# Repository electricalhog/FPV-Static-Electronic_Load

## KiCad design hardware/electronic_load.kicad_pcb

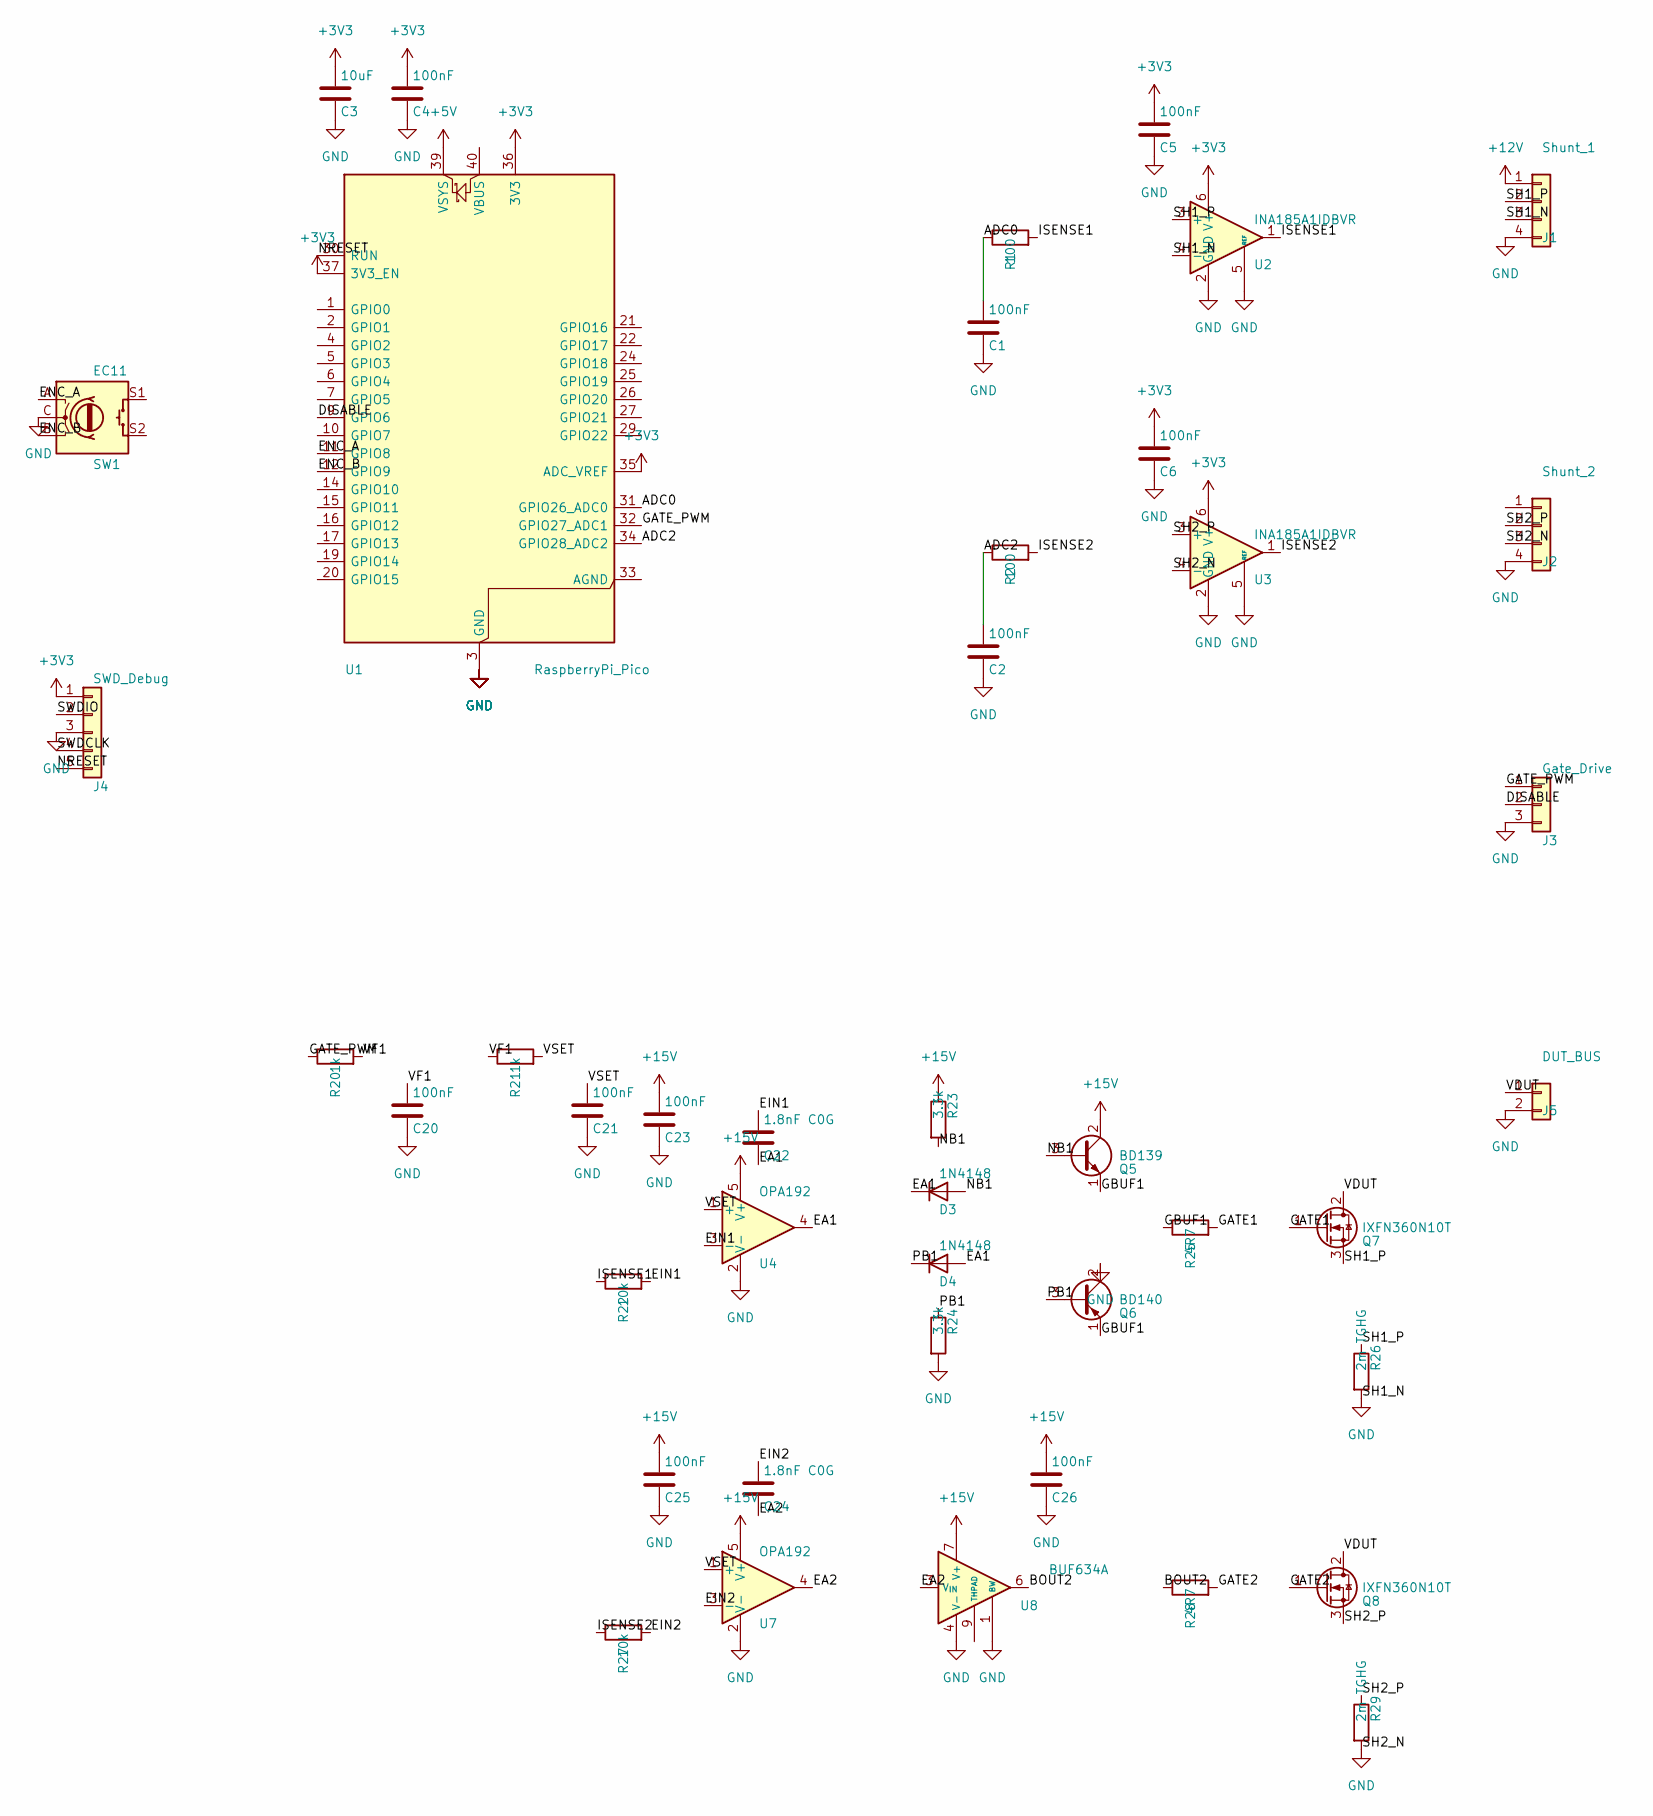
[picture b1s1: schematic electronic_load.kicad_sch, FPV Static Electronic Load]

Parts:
C1, C2, C4, C5, C6, C20, C21, C23, C25, C26: 100nF; C_0603_1608Metric
C3: 10uF; C_0805_2012Metric
C22, C24: 1.8nF C0G; C_0603_1608Metric
D3, D4: 1N4148; D_DO-35_SOD27_P7.62mm_Horizontal
J1: Shunt_1; PinHeader_1x04_P2.54mm_Vertical
J2: Shunt_2; PinHeader_1x04_P2.54mm_Vertical
J3: Gate_Drive; PinHeader_1x03_P2.54mm_Vertical
J4: SWD_Debug; PinHeader_1x05_P2.54mm_Vertical
J5: DUT_BUS; PinHeader_1x02_P2.54mm_Vertical
Q5: BD139; TO-126-3_Vertical
Q6: BD140; TO-126-3_Vertical
Q7, Q8: IXFN360N10T; SOT-227
R1, R2: 100; R_0603_1608Metric
R20, R21: 1k; R_0603_1608Metric
R22, R27: 10k; R_0603_1608Metric
R23, R24: 3.3k; R_0603_1608Metric
R25, R28: 4R7; R_0603_1608Metric
R26, R29: 2m TGHG; SOT-227
SW1: EC11; RotaryEncoder_Alps_EC11E-Switch_Vertical_H20mm
U1: RaspberryPi_Pico
U2, U3: INA185A1IDBVR; SOT-23-5
U4, U7: OPA192; SOT-23-5
U8: BUF634A; HSOP-8-1EP_3.9x4.9mm_P1.27mm_EP2.41x3.1mm

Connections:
+3V3: C3.1, C4.1, C5.1, C6.1, J4.1, U1.35 (ADC_VREF), U1.36 (3V3), U1.37 (3V3_EN), U2.6 (V+), U3.6 (V+)
+5V: U1.39 (VSYS)
+12V: J1.1
+15V: C23.1, C25.1, C26.1, Q5.2 (C), R23.1, U4.5 (V+), U7.5 (V+), U8.7 (V+)
/ADC0: C1.1, R1.1, U1.31 (GPIO26_ADC0)
/ADC2: C2.1, R2.1, U1.34 (GPIO28_ADC2)
/BOUT2: R28.1, U8.6
/DISABLE: J3.2, U1.9 (GPIO6)
/EA1: C22.2, D3.1 (K), D4.2 (A), U4.4
/EA2: C24.2, U7.4, U8.3 (V_{IN})
/EIN1: C22.1, R22.2, U4.3 (-)
/EIN2: C24.1, R27.2, U7.3 (-)
/ENC_A: SW1.A, U1.11 (GPIO8)
/ENC_B: SW1.B, U1.12 (GPIO9)
/GATE1: Q7.1 (G), R25.2
/GATE2: Q8.1 (G), R28.2
/GATE_PWM: J3.1, R20.1, U1.32 (GPIO27_ADC1)
/GBUF1: Q5.1 (E), Q6.1 (E), R25.1
/ISENSE1: R1.2, R22.1, U2.1
/ISENSE2: R2.2, R27.1, U3.1
/NB1: D3.2 (A), Q5.3 (B), R23.2
/NRESET: J4.5, U1.30 (RUN)
/PB1: D4.1 (K), Q6.3 (B), R24.1
/SH1_P: J1.2, Q7.3 (S), R26.1, U2.3 (+)
/SH2_P: J2.2, Q8.3 (S), R29.1, U3.3 (+)
/SWDCLK: J4.4
/SWDIO: J4.2
/VDUT: J5.1, Q7.2 (D), Q8.2 (D)
/VF1: C20.1, R20.2, R21.1
/VSET: C21.1, R21.2, U4.1 (+), U7.1 (+)
GND: C1.2, C2.2, C3.2, C4.2, C5.2, C6.2, C20.2, C21.2, C23.2, C25.2, C26.2, J1.3, J1.4, J2.3, J2.4, J3.3, J4.3, J5.2, Q6.2 (C), R24.2, R26.2, R29.2, SW1.C, U1.3 (GND), U1.8 (GND), U1.13 (GND), U1.18 (GND), U1.23 (GND), U1.28 (GND), U1.38 (GND), U2.2 (GND), U2.4 (-), U2.5 (REF), U3.2 (GND), U3.4 (-), U3.5 (REF), U4.2 (V-), U7.2 (V-), U8.1 (BW), U8.4 (V-)

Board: 2 copper layers, 43 parts (0 on the bottom side), 27 nets, no tracks yet.

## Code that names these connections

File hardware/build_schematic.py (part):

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u1_adc_vref   = pin('U1', '35')          # ADC_VREF
u1_gnd        = pin('U1', '3')           # first GND
u1_agnd       = pin('U1', '33')          # AGND (analog GND)
u1_gpio6      = pin('U1', '9')           # DISABLE
u1_gpio8      = pin('U1', '11')          # ENC_A
u1_gpio9      = pin('U1', '12')          # ENC_B
u1_adc0       = pin('U1', '31')          # GPIO26_ADC0
u1_pwm        = pin('U1', '32')          # GPIO27_ADC1 → gate PWM
u1_adc2       = pin('U1', '34')          # GPIO28_ADC2
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j4 = {str(n): pin('J4', str(n)) for n in range(1, 6)}

# Additional U1 pins
u1_run    = pin('U1', '30')   # RUN / nRESET
u1_3v3_en = pin('U1', '37')   # 3V3_EN – must be pulled high to enable regulator
u1_gnd38  = pin('U1', '38')   # GND (bottom)
u1_vsys   = pin('U1', '39')   # VSYS power input (5 V supply)
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nets = [
    # Encoder quadrature to Pico
    ('ENC_A',    *sw1_a),
    ('ENC_A',    *u1_gpio8),
    ('ENC_B',    *sw1_b),
    ('ENC_B',    *u1_gpio9),

    # INA1 output → series R1 → ADC0
    ('ISENSE1',  *u2_out),
    ('ISENSE1',  *r1_ina),   # right pin of R1 (INA side)
    ('ADC0',     *r1_adc),   # left  pin of R1 (filter output)
    ('ADC0',     *u1_adc0),

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    # Gate drive (PWM5B) and load enable
    ('GATE_PWM', *u1_pwm),
    ('GATE_PWM', *j3['1']),
    ('DISABLE',  *u1_gpio6),
    ('DISABLE',  *j3['2']),

    # Shunt sense inputs to INA1
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    # SWD debug connector J4 signals
    ('SWDIO',    *j4['2']),   # J4 pin 2 – data (no matching Pico module pin)
    ('SWDCLK',   *j4['4']),   # J4 pin 4 – clock (no matching Pico module pin)
    ('NRESET',   *j4['5']),   # J4 pin 5 – reset
    ('NRESET',   *u1_run),    # U1 pin 30 (RUN) = active-high reset
]

for net, x, y in nets:
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    ('EA1',      *d3_k), ('EA1', *d4_a),          # class-AB input node
    # bias chain and output pair
    ('NB1',      *r23_b), ('NB1', *d3_a), ('NB1', *q5['3']),
    ('PB1',      *r24_t), ('PB1', *d4_k), ('PB1', *q6['3']),
    ('GBUF1',    *q5['1']), ('GBUF1', *q6['1']), ('GBUF1', *r25_l),
    ('GATE1',    *r25_r), ('GATE1', *q7['1']),
    # power FET + TGHG shunt (SOT-227 pair on shared heatsink)
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
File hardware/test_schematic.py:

"""
Schematic completeness tests for FPV Static Electronic Load.
Run:  pytest hardware/test_schematic.py -v
"""
import os, sys, glob
import pytest

SITE = '/home/daniel/.cache/uv/archive-v0/7cuypMzPSfPk6TCt/lib/python3.12/site-packages'
SCH  = '/home/daniel/GitHub/FPV-Static-Electronic_Load/hardware/electronic_load.kicad_sch'


def _find_symlib():
    """Same resolution as build_schematic.py: env var, flatpak (any hash), apt."""
    if p := os.environ.get('KICAD_SYMBOL_DIR'):
        return p
    probe = 'MCU_Module.kicad_sym'
    for m in reversed(sorted(glob.glob(
            '/var/lib/flatpak/runtime/org.kicad.KiCad.Library.Symbols'
            '/x86_64/stable/*/files/symbols'))):
        if os.path.exists(os.path.join(m, probe)):
            return m
    return '/usr/share/kicad/symbols'


SYMLIB = _find_symlib()
sys.path.insert(0, SITE)
os.environ['KICAD_SYMBOL_DIR']  = SYMLIB
os.environ['KICAD6_SYMBOL_DIR'] = SYMLIB

from kicad_sch_api import load_schematic


@pytest.fixture(scope='module')
def sch():
    return load_schematic(SCH)


# ── Net labels ──────────────────────────────────────────────────────────────

SIGNAL_NETS = [
    'ENC_A', 'ENC_B',
    'ISENSE1', 'ADC0',
    'ISENSE2', 'ADC2',
    'GATE_PWM', 'DISABLE',
    'SH1_P', 'SH1_N',
    'SH2_P', 'SH2_N',
]

SWD_NETS = ['SWDIO', 'SWDCLK', 'NRESET']

# Analog frontend (per-FET linear loops; see hardware/sim/)
ANALOG_NETS = [
    'VF1', 'VSET',                          # setpoint DAC filter
    'EIN1', 'EA1', 'NB1', 'PB1', 'GBUF1', 'GATE1',   # ch A discrete class-AB
    'EIN2', 'EA2', 'BOUT2', 'GATE2',                 # ch B BUF634A
    'VDUT',                                          # shared drain bus
]


def _label_counts(sch):
    from collections import Counter
    return Counter(l.text for l in sch.labels)


def test_signal_nets_each_appear_twice(sch):
    counts = _label_counts(sch)
    missing = [n for n in SIGNAL_NETS if counts[n] < 2]
    assert not missing, f"Nets with fewer than 2 label endpoints: {missing}"


def test_swd_nets_present(sch):
    counts = _label_counts(sch)
    missing = [n for n in SWD_NETS if counts[n] < 1]
    assert not missing, f"SWD net labels missing: {missing}"


def test_analog_nets_each_appear_twice(sch):
    counts = _label_counts(sch)
    missing = [n for n in ANALOG_NETS if counts[n] < 2]
    assert not missing, f"Analog nets with fewer than 2 label endpoints: {missing}"


def test_vdut_bus_reaches_both_fets_and_connector(sch):
    counts = _label_counts(sch)
    assert counts['VDUT'] >= 3, (
        f"VDUT should appear on Q7 drain, Q8 drain and J5: got {counts['VDUT']}"
    )


def test_both_gate_buffer_variants_present(sch):
    refs = {c.reference: c.value for c in sch.components.all()}
    # discrete class-AB variant
    assert refs.get('Q5') == 'BD139' and refs.get('Q6') == 'BD140'
    # all-in-one variant
    assert refs.get('U8', '').startswith('BUF634')
    # both power FETs and TGHG shunts
    assert refs.get('Q7') == 'IXFN360N10T' and refs.get('Q8') == 'IXFN360N10T'
    assert refs.get('R26') == '2m TGHG' and refs.get('R29') == '2m TGHG'


# ── Power symbols ───────────────────────────────────────────────────────────

def test_power_symbols_use_pwr_reference(sch):
    bad = [
        comp.reference
        for comp in sch.components.all()
        if comp.lib_id.startswith('power:')
        and not comp.reference.startswith('#PWR')
    ]
    assert not bad, f"Power symbols with wrong reference prefix: {bad}"


# ── U1 Pico power/control pins ──────────────────────────────────────────────

def _power_lib_ids_at(sch, x, y, tol=0.5):
    return [
        c.lib_id for c in sch.components.all()
        if c.lib_id.startswith('power:')
        and abs(c.position.x - x) < tol
        and abs(c.position.y - y) < tol
    ]


def test_u1_vsys_has_power_symbol(sch):
    # U1 pin 39 (VSYS) must have a power symbol placed at its position
    pos = sch.get_component_pin_position('U1', '39')
    found = _power_lib_ids_at(sch, pos.x, pos.y)
    assert found, f"No power symbol at U1 VSYS pin ({pos.x}, {pos.y})"


def test_u1_run_has_nreset_label(sch):
    # U1 pin 30 (RUN) should be driven by NRESET label or tied to 3V3
    pos = sch.get_component_pin_position('U1', '30')
    labels_here = [
        l.text for l in sch.labels
        if abs(l.position.x - pos.x) < 0.5 and abs(l.position.y - pos.y) < 0.5
    ]
    pwr_here = _power_lib_ids_at(sch, pos.x, pos.y)
    assert labels_here or pwr_here, (
        f"U1 RUN pin ({pos.x}, {pos.y}) has neither a label nor a power symbol"
    )


def test_u1_remaining_gnd_pins_connected(sch):
    # Passive GND pins: 8, 13, 18, 23, 28, 38
    gnd_pins = ['8', '13', '18', '23', '28', '38']
    missing = []
    for pnum in gnd_pins:
        pos = sch.get_component_pin_position('U1', pnum)
        found = _power_lib_ids_at(sch, pos.x, pos.y)
        if not found:
            missing.append(pnum)
    assert not missing, f"U1 GND pins without power symbols: {missing}"


# ── RC filter wires ─────────────────────────────────────────────────────────

def test_rc_filter_wires_exist(sch):
    wires = list(sch.wires)
    assert len(wires) >= 2, "Expected ≥2 RC filter wires (R→C stubs)"


def test_rc_filter_wires_are_vertical(sch):
    for w in sch.wires:
        pts = w.points
        assert abs(pts[0].x - pts[1].x) < 0.01, (
            f"RC filter wire should be vertical, got x={pts[0].x} vs {pts[1].x}"
        )

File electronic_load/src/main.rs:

#![no_std]
#![no_main]

use panic_halt as _;
use rp2040_hal as hal;
use hal::pac;
use embedded_hal::{digital::OutputPin, pwm::SetDutyCycle};
use embedded_hal_0_2::adc::OneShot;
use rotary_encoder_embedded::{Direction, RotaryEncoder};

#[link_section = ".boot2"]
#[used]
pub static BOOT2: [u8; 256] = rp2040_boot2::BOOT_LOADER_GENERIC_03H;

// ── Tuning constants ──────────────────────────────────────────────────────────

/// Control loop sample period. 500 µs = 2 kHz.
const SAMPLE_PERIOD_US: u64 = 500;

/// Current setpoint change per encoder click, milliamps.
const ENCODER_STEP_MA: u32 = 100;

/// Hard ceiling on the setpoint, milliamps.
const MAX_SETPOINT_MA: u32 = 20_000;

/// Soft-start ramp: milliamps added to the active setpoint per control tick.
/// At 2 kHz: 10 mA × 2000 ticks/s = 20 A/s ramp rate.
const SOFT_START_RAMP_MA_PER_TICK: u32 = 10;

/// Overcurrent fault margin above the active setpoint, milliamps.
/// If measured current exceeds (setpoint + this value), the load latches off.
const OVERCURRENT_FAULT_MA: u32 = 2_000;

// ── ADC calibration ───────────────────────────────────────────────────────────
//
// The INA amplifier output is linear: 0 V → 0 mA, Vout_max → MAX_SETPOINT_MA.
// Compute ADC_COUNTS_AT_MAX_MA from your circuit:
//   counts = (Vout_at_max_current / Vref) × 4095
//
// Example — INA194 A1 (gain = 50), Rshunt = 1 mΩ, Imax = 20 A:
//   Vout = 50 × 0.001 × 20 = 1.0 V  →  counts = (1.0 / 3.3) × 4095 ≈ 1241

const ADC_COUNTS_AT_MAX_MA: u32 = 1241;

// ── PI controller gains ───────────────────────────────────────────────────────
//
// Integer arithmetic scaled by GAIN_SCALE avoids floating point while
// preserving sub-unit resolution in the gains.
//
// Tuning procedure:
//   1. Set KI = 0.  Increase KP until current tracks without oscillation.
//   2. Freeze KP.   Slowly raise KI until steady-state error reaches zero.
//      If the output starts hunting, reduce KI.
//
// The anti-windup clamp (inside PiController::update) keeps the integrator
// within the PWM output range so recovery from saturation is immediate.

const GAIN_SCALE: i64 = 1_000;

/// Proportional gain × GAIN_SCALE.  (PWM counts per mA of error)
const KP: i64 = 3;

/// Integral gain × GAIN_SCALE.  (PWM counts per mA per tick)
/// Start at 0 and increase after KP is stable.
const KI: i64 = 0;

// ─────────────────────────────────────────────────────────────────────────────

struct PiController {
    integral: i64,
}

impl PiController {
    const fn new() -> Self {
        Self { integral: 0 }
    }

    /// One PI update step.
    ///
    /// `error_ma`   – signed error: setpoint minus measured current, milliamps.
    /// `max_output` – PWM top value from `channel.max_duty_cycle()`.
    ///
    /// Returns the new PWM duty cycle clamped to `[0, max_output]`.
    fn update(&mut self, error_ma: i32, max_output: u16) -> u16 {
        let ceiling = max_output as i64 * GAIN_SCALE;

        self.integral += KI * error_ma as i64;
        // Anti-windup: the integrator alone cannot exceed output limits, so
        // once the error reverses the output responds in one tick.
        self.integral = self.integral.clamp(0, ceiling);

        let output = (KP * error_ma as i64 + self.integral) / GAIN_SCALE;
        output.clamp(0, max_output as i64) as u16
    }

    fn reset(&mut self) {
        self.integral = 0;
    }
}

// ─────────────────────────────────────────────────────────────────────────────

#[rp2040_hal::entry]
fn main() -> ! {
    let mut pac = pac::Peripherals::take().unwrap();

    let mut watchdog = hal::Watchdog::new(pac.WATCHDOG);
    let clocks = hal::clocks::init_clocks_and_plls(
        12_000_000,
        pac.XOSC,
        pac.CLOCKS,
        pac.PLL_SYS,
        pac.PLL_USB,
        &mut pac.RESETS,
        &mut watchdog,
    )
    .unwrap();

    let sio = hal::Sio::new(pac.SIO);
    let pins = hal::gpio::Pins::new(
        pac.IO_BANK0,
        pac.PADS_BANK0,
        sio.gpio_bank0,
        &mut pac.RESETS,
    );

    // Rotary encoder: GPIO8 = A, GPIO9 = B
    let pin_a = pins.gpio8.into_pull_up_input();
    let pin_b = pins.gpio9.into_pull_up_input();
    let mut encoder = RotaryEncoder::new(pin_a, pin_b).into_standard_mode();

    // PWM gate drive: GPIO27 (PWM5B), phase-correct for symmetric switching
    let mut pwm_slices = hal::pwm::Slices::new(pac.PWM, &mut pac.RESETS);
    let pwm = &mut pwm_slices.pwm5;
    pwm.set_ph_correct();
    pwm.enable();
    let channel = &mut pwm.channel_b;
    channel.output_to(pins.gpio27);
    let max_duty = channel.max_duty_cycle();

    // DISABLE pin: GPIO6, active-high disables the load
    let mut disable_pin = pins.gpio6.into_push_pull_output();
    let _ = disable_pin.set_high(); // safe default: load off at startup

    // ADC: INA current sense output on GPIO26 (ADC0)
    let mut adc = hal::Adc::new(pac.ADC, &mut pac.RESETS);
    let mut current_pin =
        hal::adc::AdcPin::new(pins.gpio26.into_floating_input()).unwrap();

    // Microsecond timer for rate-gating the control loop
    let timer = hal::Timer::new(pac.TIMER, &mut pac.RESETS, &clocks);

    let mut pi = PiController::new();
    let mut setpoint_ma: u32 = 0;
    let mut active_setpoint_ma: u32 = 0; // soft-started value tracking setpoint_ma
    let mut faulted = false;
    let mut last_tick_us: u64 = timer.get_counter().ticks();

    loop {
        // ── Encoder: update demanded setpoint ────────────────────────────────
        match encoder.update() {
            Direction::Clockwise => {
                setpoint_ma = (setpoint_ma + ENCODER_STEP_MA).min(MAX_SETPOINT_MA);
            }
            Direction::Anticlockwise => {
                setpoint_ma = setpoint_ma.saturating_sub(ENCODER_STEP_MA);
            }
            Direction::None => {}
        }

        // ── Rate gate: run the control loop at a fixed sample period ─────────
        let now_us: u64 = timer.get_counter().ticks();
        if now_us.wrapping_sub(last_tick_us) < SAMPLE_PERIOD_US {
            continue;
        }
        last_tick_us = now_us;

        // ── Fault latch: stay off until power-cycled ──────────────────────────
        if faulted {
            let _ = disable_pin.set_high();
            let _ = channel.set_duty_cycle(0);
            pi.reset();
            continue;
        }

        // ── Soft start: ramp active_setpoint toward setpoint ─────────────────
        if active_setpoint_ma < setpoint_ma {
            active_setpoint_ma =
                (active_setpoint_ma + SOFT_START_RAMP_MA_PER_TICK).min(setpoint_ma);
        } else {
            // Reducing setpoint: step-down immediately (safe direction)
            active_setpoint_ma = setpoint_ma;
        }

        // ── ADC: 4× oversample to reduce quantisation noise ──────────────────
        let measured_ma = {
            let sum: u32 = (0..4u8)
                .map(|_| adc.read(&mut current_pin).unwrap_or(0) as u32)
                .sum();
            adc_to_ma(sum / 4)
        };

        // ── Overcurrent protection ────────────────────────────────────────────
        if measured_ma > active_setpoint_ma.saturating_add(OVERCURRENT_FAULT_MA) {
            faulted = true;
            continue;
        }

        // ── PI control loop ───────────────────────────────────────────────────
        if active_setpoint_ma == 0 {
            let _ = disable_pin.set_high();
            let _ = channel.set_duty_cycle(0);
            pi.reset();
        } else {
            let error_ma = active_setpoint_ma as i32 - measured_ma as i32;
            let pwm_out = pi.update(error_ma, max_duty);
            let _ = disable_pin.set_low();
            let _ = channel.set_duty_cycle(pwm_out);
        }
    }
}

/// Scale a 12-bit ADC reading linearly to milliamps.
///
/// Adjust `ADC_COUNTS_AT_MAX_MA` at the top of this file to calibrate.
#[inline]
fn adc_to_ma(counts: u32) -> u32 {
    counts.saturating_mul(MAX_SETPOINT_MA) / ADC_COUNTS_AT_MAX_MA
}

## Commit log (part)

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2021-08-13 16-bit communication
2021-08-13 Arduino IDE accommidations
2021-08-13 Arduino IDE accommodations
2021-08-15 16-bit bidirectional conmmunication
2024-06-16 rust init
2024-07-15 encoder control
2026-03-30 Initial plan
2026-03-30 Initial plan for electronic load UI and control features
    Agent-Logs-Url: https://github.com/electricalhog/FPV-Static-Electronic_Load/sessions/956d0469-6467-4cfd-b908-99615d8116b2
2026-03-30 Add multi-mode control (CC/CP/CR/CV/DIS), OLED UI, ADC measurements, and discharge-curve recording
    Agent-Logs-Url: https://github.com/electricalhog/FPV-Static-Electronic_Load/sessions/956d0469-6467-4cfd-b908-99615d8116b2
2026-03-30 Remove tracked build artifacts from git (target/ directory)
    Agent-Logs-Url: https://github.com/electricalhog/FPV-Static-Electronic_Load/sessions/956d0469-6467-4cfd-b908-99615d8116b2
